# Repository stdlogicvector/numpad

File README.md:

# NumPad

A custom built 5x4 key numpad with encoders and display.

More Info on this [Reddit Thread](https://www.reddit.com/r/MechanicalKeyboards/comments/e81bfg/custom_built_numpad_with_encoders_and_display/)

## Circuit Board

The circuit board is designed in Eagle.
For easy manufacturing, the gerber-files and SMT production files are included.

The BOM and SMT placement file (CPL) are formatted for use with JLCPCB.

Apart from the keys, encoders, display, the USB-connector and the LED matrix driver all parts can be populated by JLCPCB.
The schematic contains the LCSC partnumbers in the attributes of each part.

### JLCPCB Configuration

If you want to order PCBs from JLC-PCB with the provided gerber-files,
use the following settings after uploading the zipped gerber folder:

* Layers: 2
* Dimension: 98mm*98mm
* PCB Thickness: 1.6
* PCB Color: Choose what you want
* Impedance: no
* Surface Finish: HASL(with lead) (ENIG is also OK)
* Copper Weight: 1
* Gold Fingers: No
* Material Details: FR4-Standard Tg 130-140C
* Panel By JLCPCB: No
* Flying Probe Test: Fully Test
* Castellated Holes: no
* Different Design: 1
* Remove Order Number: Choose what you want

5 PCBs without assembly cost about 3.60€ or $4.00.

If you want to have the SMT parts populated, choose "SMT Assembly" and select "Bottom Layer".

When asked for the BOM and CPL file, upload the provided files.

Assembly and parts for 5 PCBs costs about 33.30€ or $37.10.

### Keys

All keys compatible with Cherry MX 2 or 3 pin should fit the board.
You can either use a wide 0-key or a normal 0-key and a 00-key.
The Enter-key can also be replaced by two individual keys.

Unfortunately, I forgot to include the option for a standard tall plus-key. Here you have to use two keys.

### Encoders

The encoders a standard rotary encoders, just search ebay/aliexpress/amazon or your local electronics dealer.

### Display

The display is an 0.91" 128x32 SPI OLED module like [this](https://www.ebay.com/itm/312892164528). They are all over ebay and aliexpress.

### Misc Parts

The USB Connector can be found on [Digikey](https://www.digikey.com/short/p12hh9), but you can substitute others with the same pad layout.

The LED Driver is also available on [Digikey](https://www.digikey.com/short/p12hhw).

## QMK Configuration

The folder qmk_config contains the configuration and code to build QMK for the NumPad.
Just put this folder in qmk/keyboards and run

```
make numpad/v1:default
```	
	
## Case

The case can be 3D printed in two parts.
There are holes for heat-set M3 threaded inserts to hold the PCB and M2 threaded inserts to hold the plate.

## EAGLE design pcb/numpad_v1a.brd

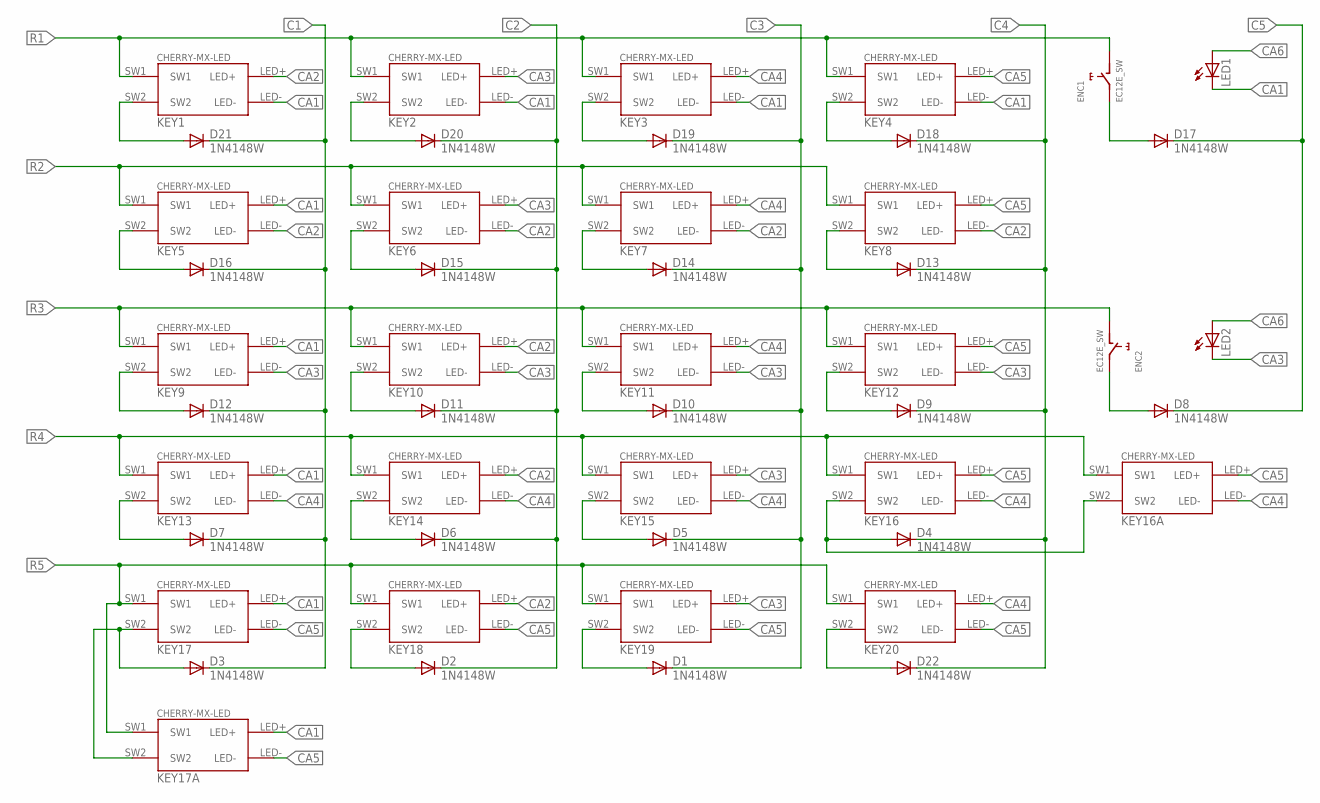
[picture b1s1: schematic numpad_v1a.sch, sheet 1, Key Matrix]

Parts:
D1, D2, D3, D4, D5, D6, D7, D8, D9, D10, D11, D12, D13, D14, D15, D16, D17, D18, D19, D20, D21, D22: 1N4148W; SOD123; LCSC C81598
ENC1, ENC2: EC12E_SW; ALPS_EC12E_SW
KEY1, KEY2, KEY3, KEY4, KEY5, KEY6, KEY7, KEY8, KEY9, KEY10, KEY11, KEY12, KEY13, KEY14, KEY15, KEY16A, KEY17, KEY18, KEY19, KEY20: CHERRY-MX-LED
KEY16, KEY17A: CHERRY-MX-LED_NOHOLES
LED1, LED2: LED3MM

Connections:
C1: D3.C, D7.C, D12.C, D16.C, D21.C; also elsewhere on the board
C2: D2.C, D6.C, D11.C, D15.C, D20.C; also elsewhere on the board
C3: D1.C, D5.C, D10.C, D14.C, D19.C; also elsewhere on the board
C4: D4.C, D9.C, D13.C, D18.C, D22.C; also elsewhere on the board
C5: D8.C, D17.C; also elsewhere on the board
CA1: KEY1.LED-, KEY2.LED-, KEY3.LED-, KEY4.LED-, KEY5.LED+, KEY9.LED+, KEY13.LED+, KEY17.LED+, KEY17A.LED+, LED1.K (C); also elsewhere on the board
CA2: KEY1.LED+, KEY5.LED-, KEY6.LED-, KEY7.LED-, KEY8.LED-, KEY10.LED+, KEY14.LED+, KEY18.LED+; also elsewhere on the board
CA3: KEY2.LED+, KEY6.LED+, KEY9.LED-, KEY10.LED-, KEY11.LED-, KEY12.LED-, KEY15.LED+, KEY19.LED+, LED2.K (C); also elsewhere on the board
CA4: KEY3.LED+, KEY7.LED+, KEY11.LED+, KEY13.LED-, KEY14.LED-, KEY15.LED-, KEY16.LED-, KEY16A.LED-, KEY20.LED+; also elsewhere on the board
CA5: KEY4.LED+, KEY8.LED+, KEY12.LED+, KEY16.LED+, KEY16A.LED+, KEY17.LED-, KEY17A.LED-, KEY18.LED-, KEY19.LED-, KEY20.LED-; also elsewhere on the board
CA6: LED1.A, LED2.A; also elsewhere on the board
unnamed: D21.A, KEY1.SW2
unnamed: D16.A, KEY5.SW2
unnamed: D12.A, KEY9.SW2
unnamed: D7.A, KEY13.SW2
unnamed: D15.A, KEY6.SW2
unnamed: D20.A, KEY2.SW2
unnamed: D11.A, KEY10.SW2
unnamed: D6.A, KEY14.SW2
unnamed: D5.A, KEY15.SW2
unnamed: D10.A, KEY11.SW2
unnamed: D14.A, KEY7.SW2
unnamed: D19.A, KEY3.SW2
unnamed: D8.A, ENC2.E (2)
unnamed: D17.A, ENC1.E (2)
unnamed: D3.A, KEY17.SW2, KEY17A.SW2
unnamed: D2.A, KEY18.SW2
unnamed: D1.A, KEY19.SW2
unnamed: D4.A, KEY16.SW2, KEY16A.SW2
unnamed: D9.A, KEY12.SW2
unnamed: D13.A, KEY8.SW2
unnamed: D18.A, KEY4.SW2
unnamed: D22.A, KEY20.SW2
R1: ENC1.D (1), KEY1.SW1, KEY2.SW1, KEY3.SW1, KEY4.SW1; also elsewhere on the board
R2: KEY5.SW1, KEY6.SW1, KEY7.SW1, KEY8.SW1; also elsewhere on the board
R3: ENC2.D (1), KEY9.SW1, KEY10.SW1, KEY11.SW1, KEY12.SW1; also elsewhere on the board
R4: KEY13.SW1, KEY14.SW1, KEY15.SW1, KEY16.SW1, KEY16A.SW1; also elsewhere on the board
R5: KEY17.SW1, KEY17A.SW1, KEY18.SW1, KEY19.SW1, KEY20.SW1; also elsewhere on the board

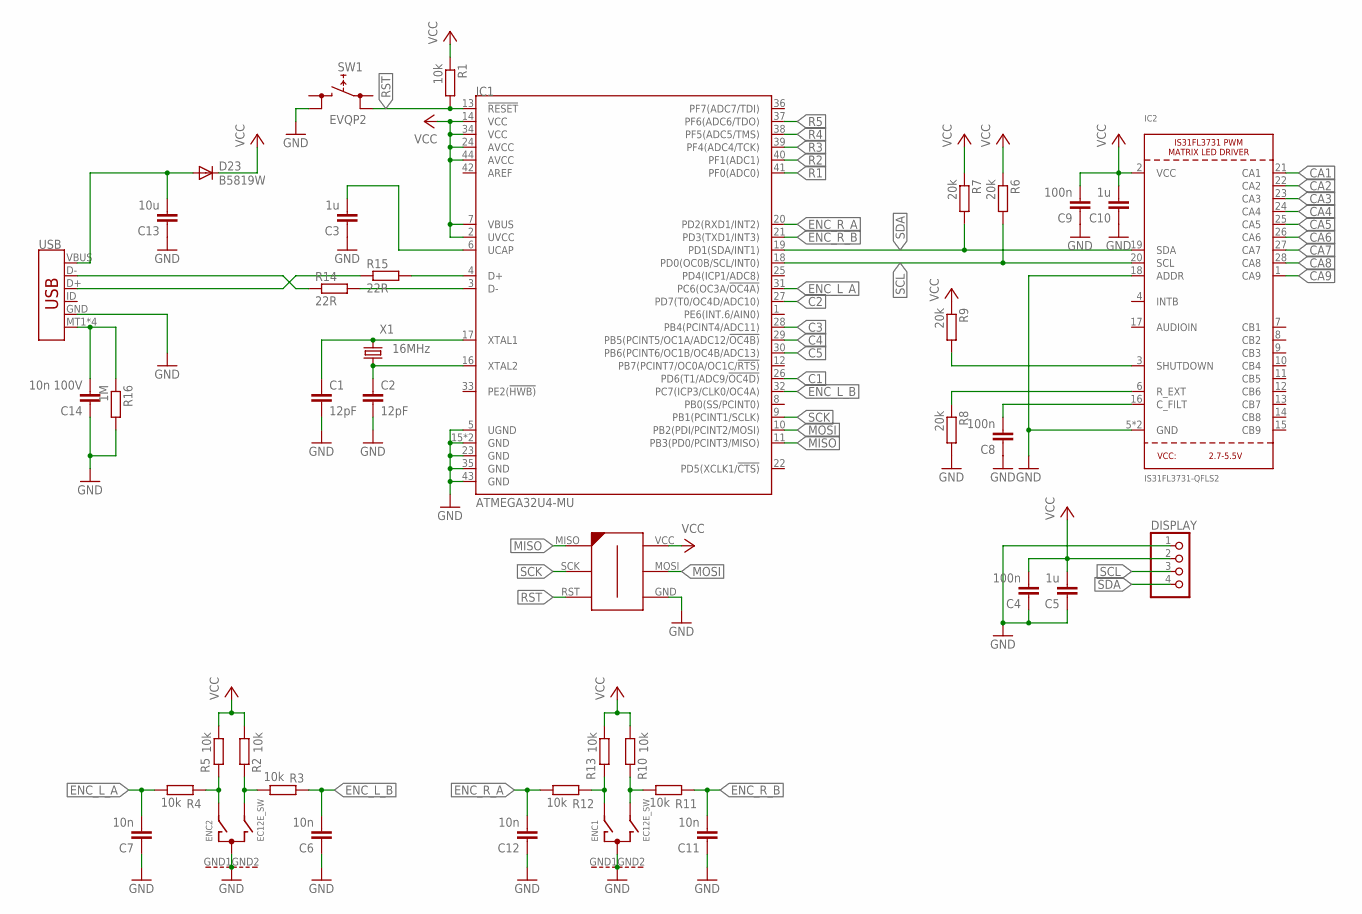
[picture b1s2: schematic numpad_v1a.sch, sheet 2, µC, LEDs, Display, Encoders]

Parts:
C1, C2: 12pF; C0603; LCSC C38523
C3, C5, C10: 1u; C0603; LCSC C15849
C4, C8, C9: 100n; C0603; LCSC C14663
C6, C7, C11, C12: 10n; C0603; LCSC C57112
C13: 10u; C0603; LCSC C19702
C14: 10n 100V; C0603; LCSC C84709
D23: B5819W; SOD123; LCSC C8598
DISPLAY: PINHD-1X4; 1X04
ENC1, ENC2: EC12E_SW; ALPS_EC12E_SW
IC1: ATMEGA32U4-MU; QFN44G-0.5-7X7MM; LCSC C112161
IC2: IS31FL3731-QFLS2; QFN28_4MM_0.4MM
ISP: AVR-ISP-6-EDGE; 6PAD_ISP
R1, R2, R3, R4, R5, R10, R11, R12, R13: 10k; R0603; LCSC C25804
R6, R7, R8, R9: 20k; R0603; LCSC C4184
R14, R15: 22R; R0603; LCSC C23345
R16: 1M; R0603; LCSC C22935
SW1: EVQP2; FARNELL 2079559
USB: USB_MICRO-B_SMT; USB-MICROB; DIGIKEY 609-4052-1-ND
X1: 16MHz; 3.2X2.5_KX-7; LCSC C13738

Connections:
C1: IC1.26 (PD6(T1/ADC9/!OC4D)); also elsewhere on the board
C2: IC1.27 (PD7(T0/OC4D/ADC10)); also elsewhere on the board
C3: IC1.28 (PB4(PCINT4/ADC11)); also elsewhere on the board
C4: IC1.29 (PB5(PCINT5/OC1A/ADC12/!OC4B)); also elsewhere on the board
C5: IC1.30 (PB6(PCINT6/OC1B/OC4B/ADC13)); also elsewhere on the board
CA1: IC2.21 (CA1); also elsewhere on the board
CA2: IC2.22 (CA2); also elsewhere on the board
CA3: IC2.23 (CA3); also elsewhere on the board
CA4: IC2.24 (CA4); also elsewhere on the board
CA5: IC2.25 (CA5); also elsewhere on the board
CA6: IC2.26 (CA6); also elsewhere on the board
CA7: IC2.27 (CA7)
CA8: IC2.28 (CA8)
CA9: IC2.1 (CA9)
ENC_L_A: C7.2, IC1.31 (PC6(OC3A/!OC4A)), R4.1
ENC_L_B: C6.2, IC1.32 (PC7(ICP3/CLK0/OC4A)), R3.2
ENC_R_A: C12.2, IC1.20 (PD2(RXD1/INT2)), R12.1
ENC_R_B: C11.2, IC1.21 (PD3(TXD1/INT3)), R11.2
GND: C1.2, C2.2, C3.1, C4.1, C5.1, C6.1, C7.1, C8.1, C9.1, C10.1, C11.1, C12.1, C13.1, C14.1, DISPLAY.1, ENC1.C, ENC1.GND1 (G), ENC1.GND2 (G), ENC2.C, ENC2.GND1 (G), ENC2.GND2 (G), IC1.5 (UGND), IC1.15 (GND), IC1.23 (GND), IC1.35 (GND), IC1.43 (GND), IC1.TAB (GND), IC2.5 (GND), IC2.18 (ADDR), IC2.THERMAL (GND), ISP.GND, R8.2, R16.2, SW1.2 (1), USB.GND
MISO: IC1.11 (PB3(PD0/PCINT3/MISO)), ISP.MISO
MOSI: IC1.10 (PB2(PDI/PCINT2/MOSI)), ISP.MOSI
unnamed: IC1.4 (D+), R15.2
unnamed: IC1.3 (D-), R14.2
unnamed: R14.1, USB.D-
unnamed: R15.1, USB.D+
unnamed: C1.1, IC1.17 (XTAL1), X1.3 (2)
unnamed: C13.2, D23.A, USB.VBUS
unnamed: C2.1, IC1.16 (XTAL2), X1.1
unnamed: C3.2, IC1.6 (UCAP)
unnamed: IC2.6 (R_EXT), R8.1
unnamed: C8.2, IC2.16 (C_FILT)
unnamed: IC2.3 (SHUTDOWN), R9.2
unnamed: ENC2.A, R4.2, R5.2
unnamed: ENC1.A, R12.2, R13.2
unnamed: ENC2.B, R2.2, R3.1
unnamed: ENC1.B, R10.2, R11.1
unnamed: C14.2, R16.1, USB.MT1 (SHIELD), USB.MT2 (SHIELD), USB.P$1 (SHIELD), USB.P$2 (SHIELD)
R1: IC1.41 (PF0(ADC0)); also elsewhere on the board
R2: IC1.40 (PF1(ADC1)); also elsewhere on the board
R3: IC1.39 (PF4(ADC4/TCK)); also elsewhere on the board
R4: IC1.38 (PF5(ADC5/TMS)); also elsewhere on the board
R5: IC1.37 (PF6(ADC6/TDO)); also elsewhere on the board
RST: IC1.13 (!RESET), ISP.RST, R1.2, SW1.3 (0)
SCK: IC1.9 (PB1(PCINT1/SCLK)), ISP.SCK
SCL: DISPLAY.3, IC1.18 (PD0(OC0B/SCL/INT0)), IC2.20 (SCL), R6.2
SDA: DISPLAY.4, IC1.19 (PD1(SDA/INT1)), IC2.19 (SDA), R7.2
VCC: C4.2, C5.2, C9.2, C10.2, D23.C, DISPLAY.2, IC1.2 (UVCC), IC1.7 (VBUS), IC1.14 (VCC), IC1.24 (AVCC), IC1.34 (VCC), IC1.44 (AVCC), IC2.2 (VCC), ISP.VCC, R1.1, R2.1, R5.1, R6.1, R7.1, R9.1, R10.1, R13.1

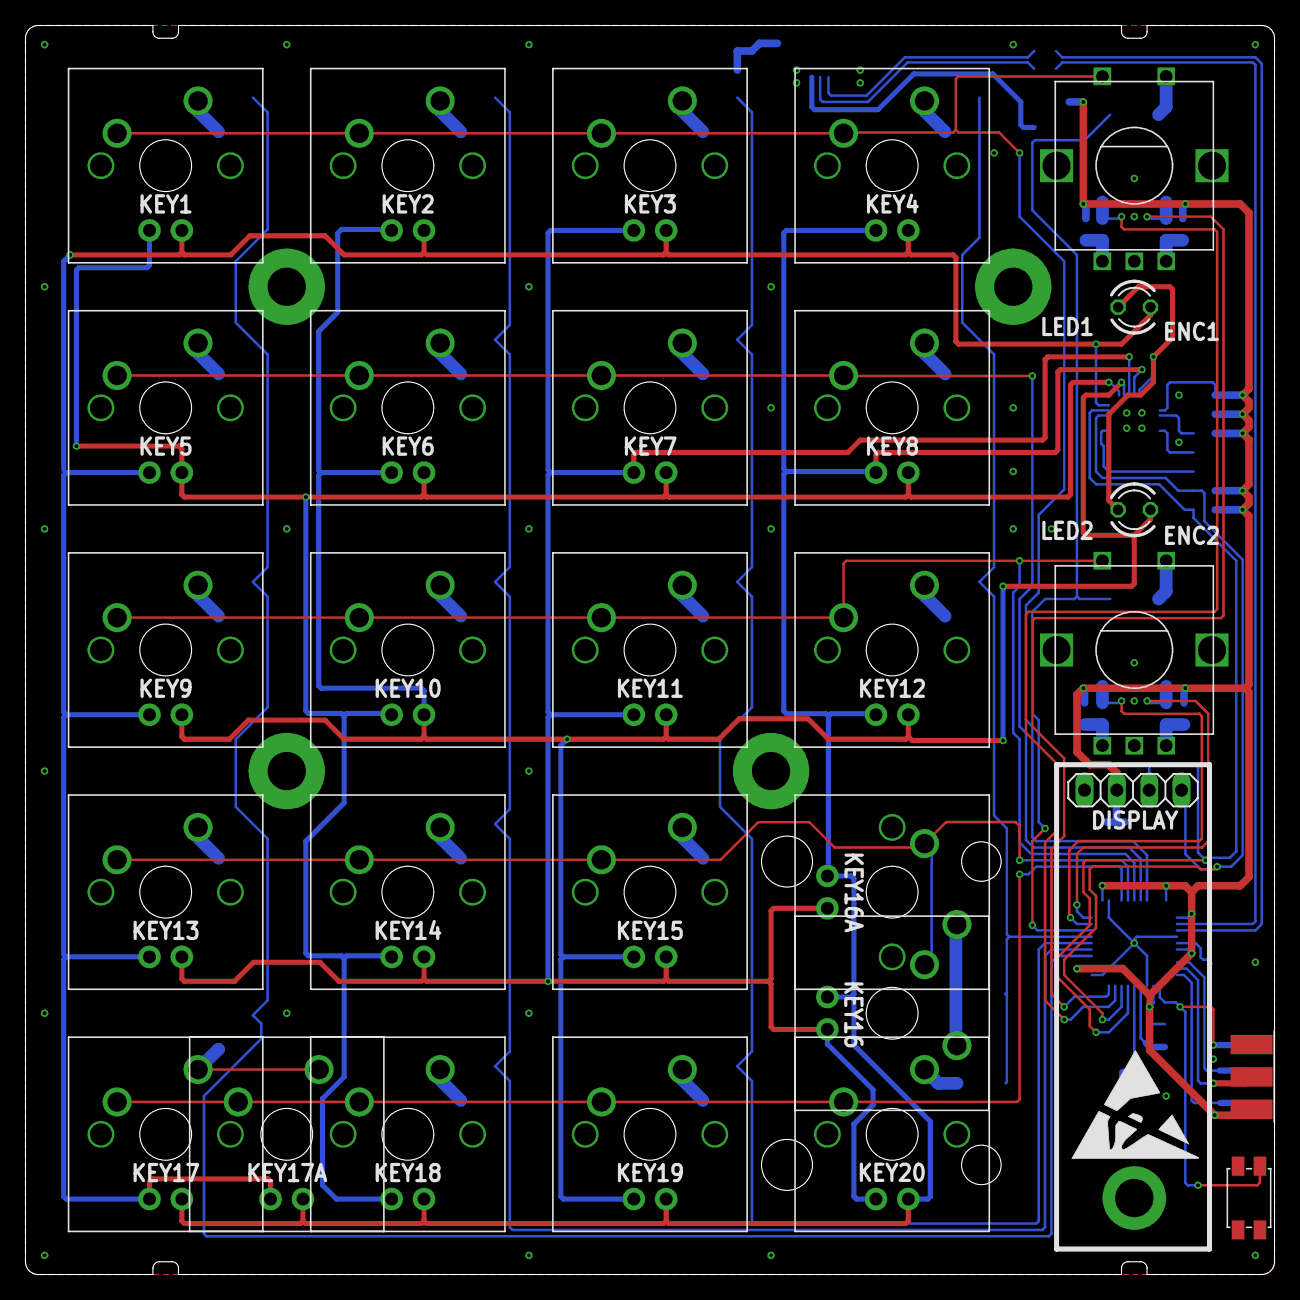
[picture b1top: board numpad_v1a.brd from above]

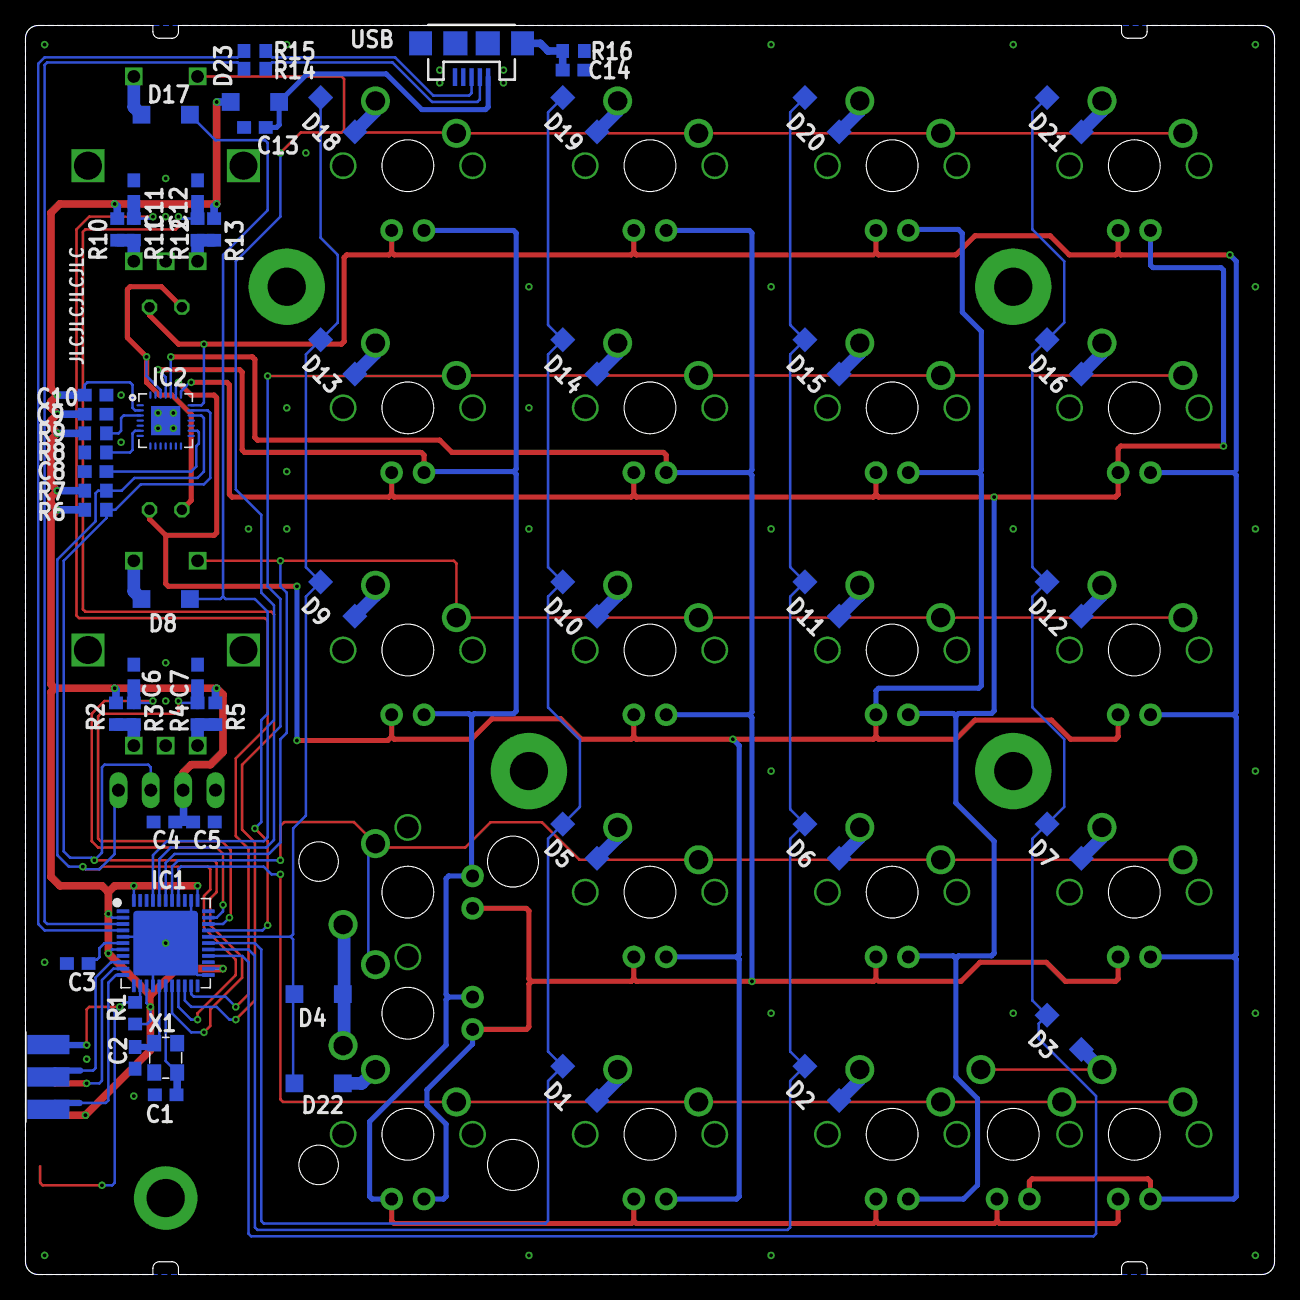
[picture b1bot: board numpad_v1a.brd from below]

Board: 2 copper layers, 98.0 x 98.0 mm, 87 parts (58 on the bottom side), 66 nets.

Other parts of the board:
U$1: ESD_10.00

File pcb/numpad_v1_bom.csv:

Comment,Designator,Footprint,LCSC
1M,R16,0603_R,C22935
1N4148W,"D1, D2, D3, D4, D5, D6, D7, D8, D9, D10, D11, D12, D13, D14, D15, D16, D17, D18, D19, D20, D21",SOD-123,C81598
1u,"C3, C5, C10",0603_C,C15849
10k,"R1, R2, R3, R4, R5, R10, R11, R12, R13",0603_R,C25804
10n,"C6, C7, C11, C12",0603_C,C57112
10n 100V,C14,0603_C,C84709
10u,C13,0603_C,C19702
12pF,"C1, C2",0603_C,C38523
16MHz,X1,SMD-3225_4P,C13738
20k,"R6, R7, R8, R9",0603_R,C4184
22R,"R14, R15",0603_R,C23345
100n,"C4, C8, C9",0603_C,C14663
ATMEGA32U4-MU,IC1,QFN-44_EP_7x7x0.5P,C112161
B5819W,D22,SOD-123,C8598

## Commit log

2019-12-12 First Revision
2019-12-12 fix(qmk_config/readme.md):Image-URL
2019-12-12 add(pcb): Schematic PDF
2019-12-12 fix(misc):Remove tmp files
2019-12-12 fix(pcb):Remove old gerbers
2019-12-12 fix(pcb): Both sheets in schematic
2019-12-12 feat(readme): Add reddit link
2019-12-12 add(gitignore): Added gitignore
2019-12-16 add(readme): JLCPCB Order Config
2019-12-17 add(readme): Fix typo, add links to parts
2019-12-18 add(cover_4x5): Added 20-key cover
2019-12-18 fix(schematic): Corrected LED driver part number
2019-12-29 fix(readme): Links fixed

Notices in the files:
parts and their libraries:
crystal-geyer_V1_0: Copyright: Geyer-Electronic
microbuilder: This work is placed in the public domain, and may be freely used for commercial and non-commercial work with the following conditions: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
